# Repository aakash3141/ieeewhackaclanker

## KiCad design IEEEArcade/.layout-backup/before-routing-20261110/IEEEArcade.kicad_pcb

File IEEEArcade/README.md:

# IEEE Arcade

Open **IEEEArcade.kicad_pro** in KiCad. The main schematic, PCB and all five child sheets are required: button_bank_1–4.kicad_sch and scoreboard.kicad_sch. Keep Arcade.kicad_sym, Arcade.pretty, fp-lib-table and sym-lib-table with the project.

## Purchasing and assembly

- [DigiKey cart](Review/DigiKey-cart.html) and [upload CSV](Review/DigiKey-board-cart.csv).
- [Detailed BOM](Review/BOM.html), [part details](Review/DigiKey-board-details.csv), and [optional harness parts](Review/DigiKey-optional-harness.csv).
- [Design review](Review/DESIGN_REVIEW.md), [display wiring](Review/DISPLAY_WIRING.md), and [I/O notes](Review/IO_REVISION.md).
- Project Information retains the original project brief, BOM workbook, manufacturer datasheets, display reference photos and meeting documents.

## PCB status

Read [routing notes](Review/ROUTING.md) and the retained final reports before fabrication. These record the previous checks and unresolved design items; the cleanup did not rerun electrical validation or certify hardware. In particular, the routing notes document a deferred display supply source and existing footprint/parity warnings.

Current artwork: [3D preview](Review/PCB-routed-3D.png), [front copper](Review/PCB-routed-top.svg), [ground plane](Review/PCB-routed-ground.svg).

## Cleanup

On November 13, 2026, historical backups, browser caches, intermediate revision outputs, unused prototype sheets, obsolete scripts, local editor preferences and stale manufacturing outputs were moved to the Windows Recycle Bin. Editable design and library files were verified unchanged, and all six active schematic sheets remain available. Parent-repository Git history was retained. Generate fresh Gerbers/drill files from the current PCB before ordering boards.

The BOM generator and its helper, netlist and mating-part inputs remain in Review so the purchasing artifacts can be regenerated. Historical baseline-dependent audit/placement generators were removed together with their backups.

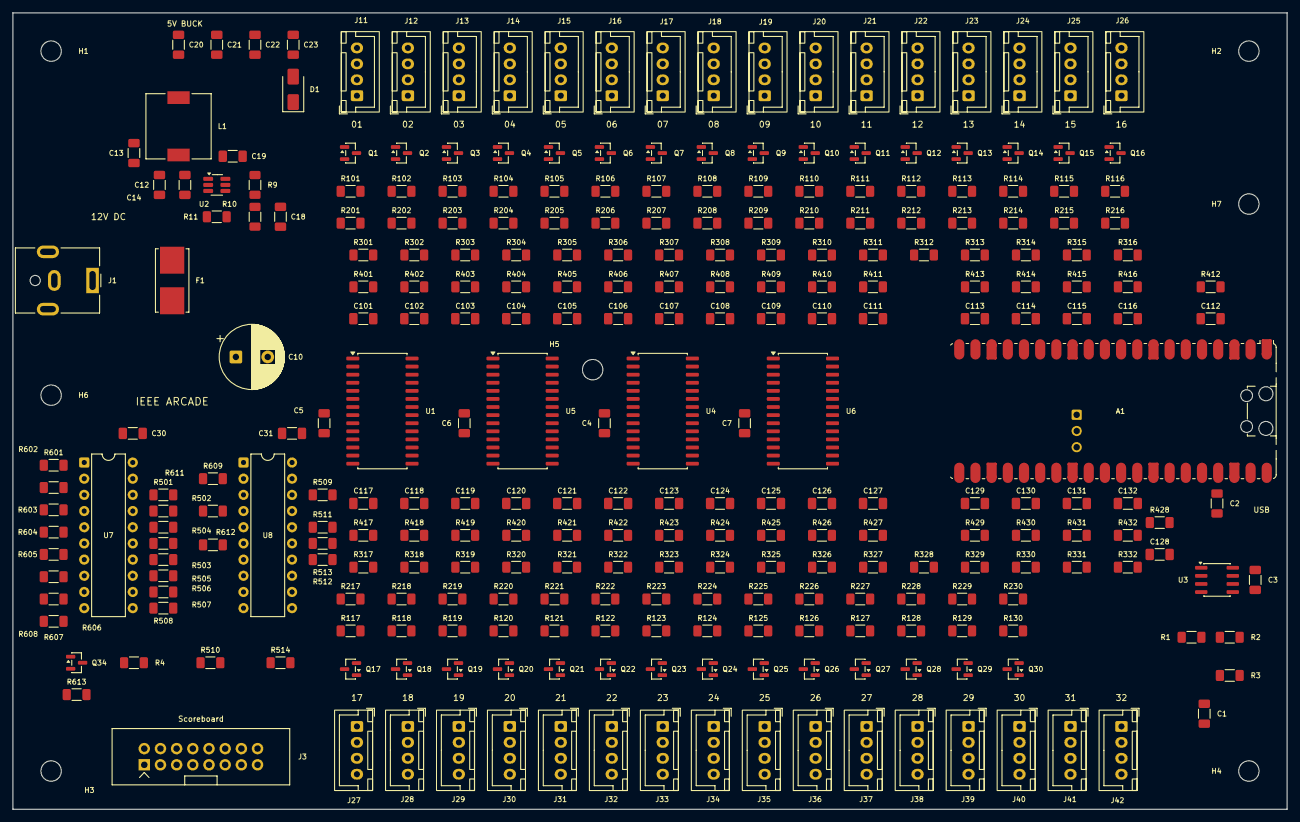
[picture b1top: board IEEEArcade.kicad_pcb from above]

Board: 4 copper layers, 200.0 x 125.0 mm, 292 parts (0 on the bottom side), 206 nets, no tracks yet.

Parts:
A1: Pico 2 W / SC1633; RaspberryPi_Pico_W_SMD_HandSolder
C1, C12, C13, C20, C21, C22, C23: 10u; C_1206_3216Metric_Pad1.33x1.80mm_HandSolder
C2, C3, C4, C5, C6, C7, C14, C19, C30, C31: 100n; C_1206_3216Metric_Pad1.33x1.80mm_HandSolder
C10: 470u; CP_Radial_D10.0mm_P5.00mm
C18: 75p; C_1206_3216Metric_Pad1.33x1.80mm_HandSolder
C101, C102, C103, C104, C105, C106, C107, C108, C109, C110, C111, C112, C113, C114, C115, C116, C117, C118, C119, C120, C121, C122, C123, C124, C125, C126, C127, C128, C129, C130, C131, C132: 10n / 50V; C_1206_3216Metric_Pad1.33x1.80mm_HandSolder
D1: SS14 / VSYS OR-ing; D_SMA
F1: 5A/25VDC fast; Fuseholder_Littelfuse_Nano2_154x
H1, H2, H3, H4, H5, H6, H7: M3 / 3.2mm NPTH; MountingHole_3.2mm_M3
J1: 12VDC; BarrelJack_CUI_PJ-063AH_Horizontal
J3: HUB75 / ABC / pin12 GND; IDC_3M_N2516_2x08
J11, J12, J13, J14, J15, J16, J17, J18, J19, J20, J21, J22, J23, J24, J25, J26, J27, J28, J29, J30, J31, J32, J33, J34, J35, J36, J37, J38, J39, J40: JST XH 4-pin; JST_XH_B4B-XH-A_1x04_P2.50mm_Vertical
J41, J42: MENU input only; JST_XH_B4B-XH-A_1x04_P2.50mm_Vertical
L1: 15uH; L_Wurth_7447714150
Q1, Q2, Q3, Q4, Q5, Q6, Q7, Q8, Q9, Q10, Q11, Q12, Q13, Q14, Q15, Q16, Q17, Q18, Q19, Q20, Q21, Q22, Q23, Q24, Q25, Q26, Q27, Q28, Q29, Q30, Q34: AO3400A; SOT-23
R1, R2, R301, R302, R303, R304, R305, R306, R307, R308, R309, R310, R311, R312, R313, R314, R315, R316, R317, R318, R319, R320, R321, R322, R323, R324, R325, R326, R327, R328, R329, R330, R331, R332: 4.7k; R_1206_3216Metric_Pad1.30x1.75mm_HandSolder
R3, R4, R510, R514: 10k; R_1206_3216Metric_Pad1.30x1.75mm_HandSolder
R9: 511k; R_1206_3216Metric_Pad1.30x1.75mm_HandSolder
R10, R201, R202, R203, R204, R205, R206, R207, R208, R209, R210, R211, R212, R213, R214, R215, R216, R217, R218, R219, R220, R221, R222, R223, R224, R225, R226, R227, R228, R229, R230, R601, R602, R603, R604, R605, R606, R607, R608, R609, R611, R612, R613: 100k; R_1206_3216Metric_Pad1.30x1.75mm_HandSolder
R11: 13.7k; R_1206_3216Metric_Pad1.30x1.75mm_HandSolder
R101, R102, R103, R104, R105, R106, R107, R108, R109, R110, R111, R112, R113, R114, R115, R116, R117, R118, R119, R120, R121, R122, R123, R124, R125, R126, R127, R128, R129, R130, R401, R402, R403, R404, R405, R406, R407, R408, R409, R410, R411, R412, R413, R414, R415, R416, R417, R418, R419, R420, R421, R422, R423, R424, R425, R426, R427, R428, R429, R430, R431, R432: 1k; R_1206_3216Metric_Pad1.30x1.75mm_HandSolder
R501, R502, R503, R504, R505, R506, R507, R508, R509, R511, R512, R513: 33; R_1206_3216Metric_Pad1.30x1.75mm_HandSolder
U1, U4, U5, U6: MCP23017T-E/SO; SOIC-28W_7.5x17.9mm_P1.27mm
U2: TPS54202HDDCR; SOT-23-6_Handsoldering
U3: 24LC256-I/SN; SOIC-8_3.9x4.9mm_P1.27mm
U7, U8: SN74AHCT245N; DIP-20_W7.62mm

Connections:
+3V3: A1.36 (3V3), C1.1, C2.1, C3.1, C4.1, C5.1, C6.1, C7.1, R1.1, R2.1, R3.1, R4.2, R301.1, R302.1, R303.1, R304.1, R305.1, R306.1, R307.1, R308.1, R309.1, R310.1, R311.1, R312.1, R313.1, R314.1, R315.1, R316.1, R317.1, R318.1, R319.1, R320.1, R321.1, R322.1, R323.1, R324.1, R325.1, R326.1, R327.1, R328.1, R329.1, R330.1, R331.1, R332.1, U1.9 (V_{DD}), U1.15 (A0), U3.8 (VCC), U4.9 (V_{DD}), U4.15 (A0), U4.16 (A1), U5.9 (V_{DD}), U5.16 (A1), U6.9 (V_{DD}), U6.17 (A2)
+5V: C18.1, C20.1, C21.1, C22.1, C23.1, D1.2 (A), L1.2, R10.1
+5V_DISPLAY: C30.1, C31.1, R510.1, R514.1, U7.1 (A->B), U7.20 (VCC), U8.1 (A->B), U8.20 (VCC)
+12V: C10.1, C12.1, C13.1, C14.1, F1.2, J11.1, J12.1, J13.1, J14.1, J15.1, J16.1, J17.1, J18.1, J19.1, J20.1, J21.1, J22.1, J23.1, J24.1, J25.1, J26.1, J27.1, J28.1, J29.1, J30.1, J31.1, J32.1, J33.1, J34.1, J35.1, J36.1, J37.1, J38.1, J39.1, J40.1, R9.1, U2.3 (VIN)
/I2C_SCL: A1.20 (GPIO15), R2.2, U1.12 (SCK), U3.6 (SCL), U4.12 (SCK), U5.12 (SCK), U6.12 (SCK)
/I2C_SDA: A1.19 (GPIO14), R1.2, U1.13 (SDA), U3.5 (SDA), U4.13 (SDA), U5.13 (SDA), U6.13 (SDA)
/IO_RESET_N: A1.17 (GPIO13), R3.2, U1.18 (~RESET), U4.18 (~RESET), U5.18 (~RESET), U6.18 (~RESET)
DISP_A: A1.9 (GPIO6), R607.1, U7.8 (A6)
DISP_A_5V: J3.9, R507.2
DISP_B: A1.10 (GPIO7), R608.1, U7.9 (A7)
DISP_B1: A1.4 (GPIO2), R603.1, U7.4 (A2)
DISP_B1_5V: J3.3, R503.2
DISP_B2: A1.7 (GPIO5), R606.1, U7.7 (A5)
DISP_B2_5V: J3.7, R506.2
DISP_BUF_OE_N: Q34.3 (D), R510.2, U7.19 (CE), U8.19 (CE)
DISP_B_5V: J3.10, R508.2
DISP_C: A1.11 (GPIO8), R609.1, U8.2 (A0)
DISP_CLK: A1.14 (GPIO10), R611.1, U8.4 (A2)
DISP_CLK_5V: J3.13, R511.2
DISP_C_5V: J3.11, R509.2
DISP_ENABLE: A1.12 (GPIO9), Q34.1 (G), R613.1
DISP_G1_5V: J3.2, R502.2
DISP_G2: A1.6 (GPIO4), R605.1, U7.6 (A4)
DISP_G2_5V: J3.6, R505.2
DISP_LAT: A1.15 (GPIO11), R612.1, U8.5 (A3)
DISP_LAT_5V: J3.14, R512.2
DISP_OE_N: A1.16 (GPIO12), R4.1, U8.6 (A4)
DISP_OE_N_5V: J3.15, R513.2, R514.2
DISP_R1: A1.1 (GPIO0), R601.1, U7.2 (A0)
DISP_R1_5V: J3.1, R501.2
DISP_R2: A1.5 (GPIO3), R604.1, U7.5 (A3)
DISP_R2_5V: J3.5, R504.2
GND: A1.3 (GND), A1.8 (GND), A1.13 (GND), A1.18 (GND), A1.23 (GND), A1.28 (GND), A1.38 (GND), C1.2, C2.2, C3.2, C4.2, C5.2, C6.2, C7.2, C10.2, C12.2, C13.2, C14.2, C20.2, C21.2, C22.2, C23.2, C30.2, C31.2, C101.2, C102.2, C103.2, C104.2, C105.2, C106.2, C107.2, C108.2, C109.2, C110.2, C111.2, C112.2, C113.2, C114.2, C115.2, C116.2, C117.2, C118.2, C119.2, C120.2, C121.2, C122.2, C123.2, C124.2, C125.2, C126.2, C127.2, C128.2, C129.2, C130.2, C131.2, C132.2, J1.2, J3.4, J3.8, J3.12, J3.16, J11.4, J12.4, J13.4, J14.4, J15.4, J16.4, J17.4, J18.4, J19.4, J20.4, J21.4, J22.4, J23.4, J24.4, J25.4, J26.4, J27.4, J28.4, J29.4, J30.4, J31.4, J32.4, J33.4, J34.4, J35.4, J36.4, J37.4, J38.4, J39.4, J40.4, J41.4, J42.4, Q1.2 (S), Q2.2 (S), Q3.2 (S), Q4.2 (S), Q5.2 (S), Q6.2 (S), Q7.2 (S), Q8.2 (S), Q9.2 (S), Q10.2 (S), Q11.2 (S), Q12.2 (S), Q13.2 (S), Q14.2 (S), Q15.2 (S), Q16.2 (S), Q17.2 (S), Q18.2 (S), Q19.2 (S), Q20.2 (S), Q21.2 (S), Q22.2 (S), Q23.2 (S), Q24.2 (S), Q25.2 (S), Q26.2 (S), Q27.2 (S), Q28.2 (S), Q29.2 (S), Q30.2 (S), Q34.2 (S), R11.2, R201.2, R202.2, R203.2, R204.2, R205.2, R206.2, R207.2, R208.2, R209.2, R210.2, R211.2, R212.2, R213.2, R214.2, R215.2, R216.2, R217.2, R218.2, R219.2, R220.2, R221.2, R222.2, R223.2, R224.2, R225.2, R226.2, R227.2, R228.2, R229.2, R230.2, R601.2, R602.2, R603.2, R604.2, R605.2, R606.2, R607.2, R608.2, R609.2, R611.2, R612.2, R613.2, U1.10 (V_{SS}), U1.16 (A1), U1.17 (A2), U2.1 (GND), U3.1 (A0), U3.2 (A1), U3.3 (A2), U3.4 (GND), U3.7 (WP), U4.10 (V_{SS}), U4.17 (A2), U5.10 (V_{SS}), U5.15 (A0), U5.17 (A2), U6.10 (V_{SS}), U6.15 (A0), U6.16 (A1), U7.10 (GND), U8.3 (A1), U8.7 (A5), U8.8 (A6), U8.9 (A7), U8.10 (GND)
LAMP_01: R101.2, U1.28 (GPA7)
LAMP_02: R102.2, U1.8 (GPB7)
LAMP_03: R103.2, U5.23 (GPA2)
LAMP_04: R104.2, U5.24 (GPA3)
LAMP_05: R105.2, U5.25 (GPA4)
LAMP_06: R106.2, U5.26 (GPA5)
LAMP_07: R107.2, U5.27 (GPA6)
LAMP_08: R108.2, U5.28 (GPA7)
LAMP_09: R109.1, U5.1 (GPB0)
LAMP_10: R110.1, U5.2 (GPB1)
LAMP_11: R111.1, U5.3 (GPB2)
LAMP_12: R112.1, U5.4 (GPB3)
LAMP_13: R113.1, U5.5 (GPB4)
LAMP_14: R114.1, U5.6 (GPB5)
LAMP_15: R115.1, U5.7 (GPB6)
LAMP_16: R116.1, U5.8 (GPB7)
LAMP_17: R117.1, U4.28 (GPA7)
LAMP_18: R118.1, U4.8 (GPB7)
LAMP_19: R119.1, U6.23 (GPA2)
LAMP_20: R120.1, U6.24 (GPA3)
LAMP_21: R121.1, U6.25 (GPA4)
LAMP_22: R122.1, U6.26 (GPA5)
LAMP_23: R123.1, U6.27 (GPA6)
LAMP_24: R124.1, U6.28 (GPA7)
LAMP_25: R125.1, U6.1 (GPB0)
LAMP_26: R126.1, U6.2 (GPB1)
LAMP_27: R127.1, U6.3 (GPB2)
LAMP_28: R128.1, U6.4 (GPB3)
LAMP_29: R129.1, U6.5 (GPB4)
LAMP_30: R130.1, U6.6 (GPB5)
unnamed: A1.39 (VSYS), D1.1 (K)
unnamed: F1.1, J1.1
unnamed: J11.2, Q1.3 (D)
unnamed: J11.3, R301.2, R401.2
unnamed: J12.2, Q2.3 (D)
unnamed: J12.3, R302.2, R402.2
unnamed: J13.2, Q3.3 (D)
unnamed: J13.3, R303.2, R403.2
unnamed: J14.2, Q4.3 (D)
unnamed: J14.3, R304.2, R404.2
unnamed: J15.2, Q5.3 (D)
unnamed: J15.3, R305.2, R405.2
unnamed: J16.2, Q6.3 (D)
unnamed: J16.3, R306.2, R406.2
unnamed: J17.2, Q7.3 (D)
unnamed: J17.3, R307.2, R407.2
unnamed: J18.2, Q8.3 (D)
unnamed: J18.3, R308.2, R408.2
unnamed: J19.2, Q9.3 (D)
unnamed: J19.3, R309.2, R409.1
unnamed: J20.2, Q10.3 (D)
unnamed: J20.3, R310.2, R410.1
unnamed: J21.2, Q11.3 (D)
unnamed: J21.3, R311.2, R411.1
unnamed: J22.2, Q12.3 (D)
unnamed: J22.3, R312.2, R412.1
unnamed: J23.2, Q13.3 (D)
unnamed: J23.3, R313.2, R413.1
unnamed: J24.2, Q14.3 (D)
unnamed: J24.3, R314.2, R414.1
unnamed: J25.2, Q15.3 (D)
unnamed: J25.3, R315.2, R415.1
unnamed: J26.2, Q16.3 (D)
unnamed: J26.3, R316.2, R416.1
unnamed: J27.2, Q17.3 (D)
unnamed: J27.3, R317.2, R417.1
unnamed: J28.2, Q18.3 (D)
unnamed: J28.3, R318.2, R418.1
unnamed: J29.2, Q19.3 (D)
unnamed: J29.3, R319.2, R419.1
unnamed: J30.2, Q20.3 (D)
unnamed: J30.3, R320.2, R420.1
unnamed: J31.2, Q21.3 (D)
unnamed: J31.3, R321.2, R421.1
unnamed: J32.2, Q22.3 (D)
unnamed: J32.3, R322.2, R422.1
unnamed: J33.2, Q23.3 (D)
unnamed: J33.3, R323.2, R423.1
unnamed: J34.2, Q24.3 (D)
unnamed: J34.3, R324.2, R424.1
unnamed: J35.2, Q25.3 (D)
unnamed: J35.3, R325.2, R425.1
unnamed: J36.2, Q26.3 (D)
unnamed: J36.3, R326.2, R426.1
unnamed: J37.2, Q27.3 (D)
unnamed: J37.3, R327.2, R427.1
unnamed: J38.2, Q28.3 (D)
unnamed: J38.3, R328.2, R428.1
unnamed: J39.2, Q29.3 (D)
unnamed: J39.3, R329.2, R429.1
unnamed: J40.2, Q30.3 (D)
unnamed: J40.3, R330.2, R430.1
unnamed: J41.3, R331.2, R431.1
unnamed: J42.3, R332.2, R432.1
unnamed: Q1.1 (G), R101.1, R201.1
unnamed: Q2.1 (G), R102.1, R202.1
unnamed: Q3.1 (G), R103.1, R203.1
unnamed: Q4.1 (G), R104.1, R204.1
unnamed: Q5.1 (G), R105.1, R205.1
unnamed: Q6.1 (G), R106.1, R206.1
unnamed: Q7.1 (G), R107.1, R207.1
unnamed: Q8.1 (G), R108.1, R208.1
unnamed: Q9.1 (G), R109.2, R209.1
unnamed: Q10.1 (G), R110.2, R210.1
unnamed: Q11.1 (G), R111.2, R211.1
unnamed: Q12.1 (G), R112.2, R212.1
unnamed: Q13.1 (G), R113.2, R213.1
unnamed: Q14.1 (G), R114.2, R214.1
unnamed: Q15.1 (G), R115.2, R215.1
unnamed: Q16.1 (G), R116.2, R216.1
unnamed: Q17.1 (G), R117.2, R217.1
unnamed: Q18.1 (G), R118.2, R218.1
unnamed: Q19.1 (G), R119.2, R219.1
unnamed: Q20.1 (G), R120.2, R220.1
unnamed: Q21.1 (G), R121.2, R221.1
unnamed: Q22.1 (G), R122.2, R222.1
unnamed: Q23.1 (G), R123.2, R223.1
unnamed: Q24.1 (G), R124.2, R224.1
unnamed: Q25.1 (G), R125.2, R225.1
unnamed: Q26.1 (G), R126.2, R226.1
unnamed: Q27.1 (G), R127.2, R227.1
unnamed: Q28.1 (G), R128.2, R228.1
unnamed: Q29.1 (G), R129.2, R229.1
unnamed: Q30.1 (G), R130.2, R230.1
unnamed: C19.1, U2.6 (BOOT)
unnamed: R9.2, U2.5 (EN)
unnamed: C18.2, R10.2, R11.1, U2.4 (FB)
unnamed: C19.2, L1.1, U2.2 (SW)
unnamed: R602.1, U7.3 (A1)
unnamed: R501.1, U7.18 (B0)
unnamed: R502.1, U7.17 (B1)
unnamed: R503.1, U7.16 (B2)
unnamed: R504.1, U7.15 (B3)
unnamed: R505.1, U7.14 (B4)
unnamed: R506.1, U7.13 (B5)
unnamed: R507.1, U7.12 (B6)
unnamed: R508.1, U7.11 (B7)
unnamed: R509.1, U8.18 (B0)
unnamed: R511.1, U8.16 (B2)
unnamed: R512.1, U8.15 (B3)
unnamed: R513.1, U8.14 (B4)
SW_01: C101.1, R401.1, U1.21 (GPA0)
SW_02: C102.1, R402.1, U1.22 (GPA1)
SW_03: C103.1, R403.1, U1.23 (GPA2)
SW_04: C104.1, R404.1, U1.24 (GPA3)
SW_05: C105.1, R405.1, U1.25 (GPA4)
SW_06: C106.1, R406.1, U1.26 (GPA5)
SW_07: C107.1, R407.1, U1.27 (GPA6)
SW_08: C108.1, R408.1, U1.1 (GPB0)
SW_09: C109.1, R409.2, U1.2 (GPB1)
SW_10: C110.1, R410.2, U1.3 (GPB2)
SW_11: C111.1, R411.2, U1.4 (GPB3)
SW_12: C112.1, R412.2, U1.5 (GPB4)
SW_13: C113.1, R413.2, U1.6 (GPB5)
SW_14: C114.1, R414.2, U1.7 (GPB6)
SW_15: C115.1, R415.2, U4.21 (GPA0)
SW_16: C116.1, R416.2, U4.22 (GPA1)
SW_17: C117.1, R417.2, U4.23 (GPA2)
SW_18: C118.1, R418.2, U4.24 (GPA3)
SW_19: C119.1, R419.2, U4.25 (GPA4)
SW_20: C120.1, R420.2, U4.26 (GPA5)
SW_21: C121.1, R421.2, U4.27 (GPA6)
SW_22: C122.1, R422.2, U4.1 (GPB0)
SW_23: C123.1, R423.2, U4.2 (GPB1)
SW_24: C124.1, R424.2, U4.3 (GPB2)
SW_25: C125.1, R425.2, U4.4 (GPB3)
SW_26: C126.1, R426.2, U4.5 (GPB4)
SW_27: C127.1, R427.2, U4.6 (GPB5)
SW_28: C128.1, R428.2, U4.7 (GPB6)
SW_29: C129.1, R429.2, U5.21 (GPA0)
SW_30: C130.1, R430.2, U5.22 (GPA1)
SW_31: C131.1, R431.2, U6.21 (GPA0)
SW_32: C132.1, R432.2, U6.22 (GPA1)

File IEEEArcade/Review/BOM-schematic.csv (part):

"Reference","Value","Quantity","Manufacturer","MPN","DigiKey","DigiKey URL","Datasheet","Footprint","Assembly","Verification"
"A1","Pico 2 W / SC1633","1","Raspberry Pi","SC1633","2648-SC1633CT-ND","https://www.digikey.com/en/products/detail/raspberry-pi/SC16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","https://datasheets.raspberrypi.com/picow/pico-2-w-datasheet.pdf","Module:RaspberryPi_Pico_W_SMD_HandSolder","On PCB","Pico 2 W datasheet pinout/package checked; KiCad W footprint explicitly supports Pico 2 W; DigiKey in stock 2026-11-05"
"C1,C12,C13,C20-C23","10u","7","KEMET","C1206C106K3RACTU","399-C1206C106K3RACTUCT-ND","https://www.digikey.com/en/products/detail/kemet/C1206C106K3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","https://search.kemet.com/component-documentation/download/sp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","Capacitor_SMD:C_1206_3216Metric_Pad1.33x1.80mm_HandSolder","On PCB","Datasheet pinout/package checked; DigiKey stock seen 2026-11-04"
"C2-C7,C14,C19,C30,C31","100n","10","KEMET","C1206C104K5RACTU","399-C1206C104K5RACTUCT-ND","https://www.digikey.com/en/products/detail/kemet/C1206C104K5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","https://search.kemet.com/component-documentation/download/sp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","Capacitor_SMD:C_1206_3216Metric_Pad1.33x1.80mm_HandSolder","On PCB","Datasheet pinout/package checked; DigiKey stock seen 2026-11-04"
"C10","470u","1","Panasonic Industry","EEU-FR1E471","P14419-ND","https://www.digikey.com/en/products/detail/panasonic-industr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","https://industrial.panasonic.com/cdbs/www-data/pdf/RDF0000/A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","Capacitor_THT:CP_Radial_D10.0mm_P5.00mm","On PCB","Datasheet pinout/package checked; DigiKey stock seen 2026-11-04"
"C18","75p","1","KEMET","C1206C750J5GACTU","399-14710-1-ND","https://www.digikey.com/en/products/detail/kemet/C1206C750J5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","https://search.kemet.com/component-documentation/download/sp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","Capacitor_SMD:C_1206_3216Metric_Pad1.33x1.80mm_HandSolder","On PCB","Datasheet pinout/package checked; DigiKey stock seen 2026-11-04"
"C101-C132","10n / 50V","32","KEMET","C1206C103K5RACTU","399-C1206C103K5RACTUCT-ND","https://www.digikey.com/en/products/detail/kemet/C1206C103K5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","https://search.kemet.com/component-documentation/download/sp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","Capacitor_SMD:C_1206_3216Metric_Pad1.33x1.80mm_HandSolder","On PCB","Datasheet pinout/package checked; DigiKey stock seen 2026-11-04"
"D1","SS14 / VSYS OR-ing","1","Vishay General Semiconductor","SS14-E3/61T","SS14-E3/61TGICT-ND","https://www.digikey.com/en/products/detail/vishay-general-se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","https://www.vishay.com/docs/88746/ss12.pdf","Diode_SMD:D_SMA","On PCB","Datasheet pinout/package checked; DigiKey stock seen 2026-11-04"
"F1","5A/25VDC fast","1","Littelfuse","0154005.DR","F1228CT-ND","https://www.digikey.com/en/products/detail/littelfuse-inc/01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","https://www.littelfuse.com/assetdocs/littelfuse-fuse-154-ser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","Fuse:Fuseholder_Littelfuse_Nano2_154x","Holder supplied preloaded with 5 A fuse","Datasheet pinout/package checked; DigiKey stock seen 2026-11-04"
"J1","12VDC","1","Same Sky","PJ-063AH","CP-063AH-ND","https://www.digikey.com/en/products/detail/same-sky-formerly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","https://www.sameskydevices.com/product/resource/pj-063ah.pdf","Connector_BarrelJack:BarrelJack_CUI_PJ-063AH_Horizontal","On PCB","Exact-MPN KiCad footprint, 2 contacts / 8A / 24V confirmed; manufacturer mechanical PDF retrieval blocked, dimensional cross-check remains open. Actual adapter plug/polarity unverified."
"J3","HUB75 / ABC / pin12 GND","1","3M","N2516-6002-RB","MHC16K-ND","https://www.digikey.com/en/products/detail/3m/N2516-6002-RB/755178","https://multimedia.3m.com/mws/media/330367O/3m-four-wall-hea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","Arcade:IDC_3M_N2516_2x08","16-way straight-through IDC to panel INPUT; OUTPUT header unused for one panel","Signal assignment read from DisplayConnections1.png: pin12 GND, not D; check mating-view pin1 on actual input header"
"J4","EXT 5V INPUT / BUFFERS ONLY","1","JST Sales America","B2B-XH-A","455-B2B-XH-A-ND","https://www.digikey.com/en/products/detail/jst-sales-america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","https://www.jst-mfg.com/product/pdf/eng/eXH.pdf","Connector_JST:JST_XH_B2B-XH-A_1x02_P2.50mm_Vertical","Input from external regulated 5V display supply; panel fed directly by separate high-current harness","Board-side XH mate verified; J4 is NOT the photographed 4-contact panel power connector"
"J11-J40","JST XH 4-pin","30","JST Sales America","B4B-XH-A","455-B4B-XH-A-ND","https://www.digikey.com/en/products/detail/jst-sales-america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","https://www.jst-mfg.com/product/pdf/eng/eXH.pdf","Connector_JST:JST_XH_B4B-XH-A_1x04_P2.50mm_Vertical","PCB header; mating XHP-4 + 4 SXH-001T-P0.6","Datasheet pinout/package checked; DigiKey stock seen 2026-11-04"
"J41,J42","MENU input only","2","JST Sales America","B4B-XH-A","455-B4B-XH-A-ND","https://www.digikey.com/en/products/detail/jst-sales-america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","https://www.jst-mfg.com/product/pdf/eng/eXH.pdf","Connector_JST:JST_XH_B4B-XH-A_1x04_P2.50mm_Vertical","PCB header; mating XHP-4 + 4 SXH-001T-P0.6","Input-only menu button. Pins 1/2 unused; no lamp supply or driver. Pin3 NO, pin4 COM/GND."
"L1","15uH","1","Wurth Elektronik","7447714150","732-2990-1-ND","https://www.digikey.com/en/products/detail/w%C3%BCrth-elektr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","https://www.we-online.com/components/products/datasheet/7447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","Arcade:L_Wurth_7447714150","On PCB","Datasheet pinout/package checked; DigiKey stock seen 2026-11-04"
"Q1-Q30,Q34","AO3400A","31","Alpha & Omega Semiconductor","AO3400A","785-1000-1-ND","https://www.digikey.com/en/products/detail/alpha-omega-semic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","https://www.aosmd.com/res/data_sheets/AO3400A.pdf","Package_TO_SOT_SMD:SOT-23","On PCB,On PCB; display buffer enable, GPIO9 HIGH enables","Datasheet pinout/package checked; DigiKey stock seen 2026-11-04"
"R1,R2,R301-R332","4.7k","34","YAGEO","RC1206FR-074K7L","311-4.70KFRCT-ND","https://www.digikey.com/en/products/detail/yageo/RC1206FR-07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","https://yageogroup.com/content/datasheet/asset/file/PYU-RC_G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","Resistor_SMD:R_1206_3216Metric_Pad1.30x1.75mm_HandSolder","On PCB","Datasheet pinout/package checked; DigiKey stock seen 2026-11-04"
"R3,R4,R510,R514","10k","4","YAGEO","RC1206FR-0710KL","311-10.0KFRCT-ND","https://www.digikey.com/en/products/detail/yageo/RC1206FR-07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","https://yageogroup.com/content/datasheet/asset/file/PYU-RC_G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","Resistor_SMD:R_1206_3216Metric_Pad1.30x1.75mm_HandSolder","On PCB,On PCB; keeps panel OE inactive when buffers disabled","Datasheet pinout/package checked; DigiKey stock seen 2026-11-04"
"R9","511k","1","YAGEO","RC1206FR-07511KL","311-511KFRCT-ND","https://www.digikey.com/en/products/detail/yageo/RC1206FR-07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","https://yageogroup.com/content/datasheet/asset/file/PYU-RC_G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","Resistor_SMD:R_1206_3216Metric_Pad1.30x1.75mm_HandSolder","On PCB","Datasheet pinout/package checked; DigiKey stock seen 2026-11-04"
"R10,R201-R230,R601-R612","100k","43","YAGEO","RC1206FR-07100KL","311-100KFRCT-ND","https://www.digikey.com/en/products/detail/yageo/RC1206FR-07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","https://yageogroup.com/content/datasheet/asset/file/PYU-RC_G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","Resistor_SMD:R_1206_3216Metric_Pad1.30x1.75mm_HandSolder","On PCB","Datasheet pinout/package checked; DigiKey stock seen 2026-11-04"
"R11","13.7k","1","YAGEO","RC1206FR-0713K7L","311-13.7KFRCT-ND","https://www.digikey.com/en/products/detail/yageo/RC1206FR-07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","https://yageogroup.com/content/datasheet/asset/file/PYU-RC_G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","Resistor_SMD:R_1206_3216Metric_Pad1.30x1.75mm_HandSolder","On PCB","Datasheet pinout/package checked; DigiKey stock seen 2026-11-04"
"R101-R130,R401-R432","1k","62","YAGEO","RC1206FR-071KL","311-1.00KFRCT-ND","https://www.digikey.com/en/products/detail/yageo/RC1206FR-07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","https://yageogroup.com/content/datasheet/asset/file/PYU-RC_G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","Resistor_SMD:R_1206_3216Metric_Pad1.30x1.75mm_HandSolder","On PCB","Datasheet pinout/package checked; DigiKey stock seen 2026-11-04"
"R501-R509,R511-R513","33","12","YAGEO","RC1206FR-0733RL","311-33.0FRCT-ND","https://www.digikey.com/en/products/detail/yageo/RC1206FR-07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","https://yageogroup.com/content/datasheet/asset/file/PYU-RC_G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","Resistor_SMD:R_1206_3216Metric_Pad1.30x1.75mm_HandSolder","On PCB","Datasheet pinout/package checked; DigiKey stock seen 2026-11-04"
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
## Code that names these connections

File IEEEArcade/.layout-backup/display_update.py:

from pathlib import Path
import re,uuid
exec(Path('display_inspect.py').read_text().split('for file in')[0])
def uid():return str(uuid.uuid4())
def fmt(v):return f'{v:.5f}'.rstrip('0').rstrip('.')
def at(b):return tuple(map(float,re.search(r'\(at ([^ ]+) ([^ ]+) ([^)]+)\)',b).groups()))
def move(b,x,y,angle=None):
 ox,oy,oa=at(b); dx=x-ox;dy=y-oy
 b=re.sub(r'\(at ([^ ]+) ([^ ]+) ([^)]+)\)',lambda m:f'(at {fmt(float(m[1])+dx)} {fmt(float(m[2])+dy)} {m[3]})',b)
 if angle is not None:b=re.sub(r'\(at [^ ]+ [^ ]+ [^)]+\)',f'(at {fmt(x)} {fmt(y)} {angle})',b,count=1)
 return b

def prop(b,k,v):
 return re.sub(r'(\(property "'+re.escape(k)+r'" )"(?:\\.|[^"\\])*"',lambda m:m[1]+'"'+v.replace('\\','\\\\').replace('"','\\"').replace('\n','\\n')+'"',b,count=1)
def fresh(b):return re.sub(r'\(uuid "[^"]+"\)',lambda m:f'(uuid "{uid()}")',b)
def label(name,x,y,angle=0):
 return f'(global_label "{name}" (shape bidirectional) (at {fmt(x)} {fmt(y)} {angle}) (effects (font (size 1.05 1.05)) (justify {"left" if angle==0 else "right"})) (uuid "{uid()}"))'
def wire(x1,y1,x2,y2):return f'(wire (pts (xy {fmt(x1)} {fmt(y1)}) (xy {fmt(x2)} {fmt(y2)})) (stroke (width 0) (type default)) (uuid "{uid()}"))'
def nc(x,y):return f'(no_connect (at {fmt(x)} {fmt(y)}) (uuid "{uid()}"))'
def text(t,x,y,size=1.05):
 t=t.replace('\\','\\\\').replace('"','\\"').replace('\n','\\n')
 return f'(text "{t}" (exclude_from_sim no) (at {fmt(x)} {fmt(y)} 0) (effects (font (size {size} {size})) (justify left)) (uuid "{uid()}"))'
root=Path('IEEEArcade.kicad_sch').read_text();s=Path('scoreboard.kicad_sch').read_text();bs=list(blocks(s));rb=list(blocks(root));bank=list(blocks(Path('button_bank_1.kicad_sch').read_text()))
syms={ref(b):b for b in bs if b.startswith('(symbol')}
path=re.search(r'\(path "([^"]+)"',syms['R4'])[1]
def clone(b,nr,x,y):
 oldref=ref(b);b=fresh(move(b,x,y));b=prop(b,'Reference',nr)
 b=b.replace(f'(reference "{oldref}")',f'(reference "{nr}")')
 b=re.sub(r'\(path "[^"]+"',f'(path "{path}"',b)
 return b
# Use existing verified 10k and 100k parts; no new resistor SKU.
r10=syms['R4'];q=next(b for b in bank if ref(b)=='Q1' and b.startswith('(symbol'))
q33=clone(q,'Q33',292.1,248.92)
q33=prop(q33,'Assembly','On PCB; display buffer enable, GPIO9 HIGH enables')
# Existing R510 is repurposed as 10k buffer-disable pull-up.
r510=clone(r10,'R510',294.64,232.41)
# Keep R510's symbol/pin identities for board association.
uold=re.findall(r'\(uuid "([^"]+)"\)',syms['R510']);unew=re.findall(r'\(uuid "([^"]+)"\)',r510)
for a,b in zip(unew,uold):r510=r510.replace(a,b)
r514=clone(r10,'R514',248.92,240.03)
r514=prop(r514,'Assembly','On PCB; keeps panel OE inactive when buffers disabled')
new=[]
for b in bs:
 if b.startswith('(lib_symbols'):
  # Add the existing MOSFET definition and PWR_FLAG for external supply.
  blib=next(x for x in bank if x.startswith('(lib_symbols'));rlib=next(x for x in rb if x.startswith('(lib_symbols'))
  extra=[next(x for x in blocks(blib) if x.startswith('(symbol "Transistor_FET:AO3400A"')),next(x for x in blocks(rlib) if x.startswith('(symbol "power:PWR_FLAG"'))]
  b=b[:-1]+'\n\t\t'+'\n\t\t'.join(extra)+'\n\t)'
 elif b.startswith('(title_block'): b=b.replace('Provisional 16-pin external scoreboard','Photo-matched HUB75 scoreboard / A-B-C scan')
 elif b.startswith('(symbol'):
  r=ref(b)
  if r=='R510':b=r510
  elif r in ['#PWR0055','#PWR0069']:b=label('DISP_BUF_OE_N',*at(b)[:2],180)
  elif '"power:+5V"' in b:b=label('+5V_DISPLAY',*at(b)[:2],180)
  elif r=='J3':
   b=prop(b,'Value','HUB75 / ABC / pin12 GND')
   b=prop(b,'Verification','Signal assignment read from DisplayConnections1.png: pin12 GND, not D; check mating-view pin1 on actual input header')
   b=prop(b,'Assembly','16-way straight-through IDC to panel INPUT; OUTPUT header unused for one panel')
  elif r=='J4':
   b=prop(b,'Value','EXT 5V INPUT / BUFFERS ONLY')
   b=prop(b,'Assembly','Input from external regulated 5V display supply; panel fed directly by separate high-current harness')
   b=prop(b,'Verification','Board-side XH mate verified; J4 is NOT the photographed 4-contact panel power connector')
 elif b.startswith('(global_label "DISP_D"'):
  b=label('DISP_ENABLE',48.26,177.8,180)
 elif b.startswith('(global_label "DISP_D_5V"'):
  if at(b)[0]>350:b=label('GND',*at(b)[:2])
  else:continue
 elif b.startswith('(wire'):
  pts=[tuple(map(float,m)) for m in re.findall(r'\(xy ([^ ]+) ([^)]+)\)',b)]
  if pts in [[(193.04,177.8),(283.21,177.8)],[(290.83,177.8),(307.34,177.8)],[(167.64,177.8),(48.26,177.8)]]:continue
 elif b.startswith('(text'):
  if 'A -> B: DIR high' in b:
   b=re.sub(r'\(text "(?:\\.|[^"\\])*"',lambda m:'(text "DIR high: A-to-B. /OE controlled by DISP_BUF_OE_N.\\nUnused inputs grounded; unused outputs left open."',b,count=1)
  elif 'EXTERNAL SCOREBOARD |' in b:
   b=prop(b,'dummy','dummy') # text retains UUID and placement below
   b=re.sub(r'\(text "(?:\\.|[^"\\])*"','(text "RGB SCOREBOARD | PHOTO-MATCHED HUB75 / A-B-C"',b,count=1)
  elif 'User requested an expected connector' in b:
   b=re.sub(r'\(text "(?:\\.|[^"\\])*"',lambda m:'(text "Photo: DR1/DG1/DB1, DR2/DG2/DB2, A/B/C, CLK, STB, OE. Pin12 = GND (NOT D).\\nPico PIO refresh: 6 RGB + 3 address + CLK/LAT/OE; no I2C expander. GP9 enables buffers."',b,count=1)
  elif 'J4: 1=+5 V' in b:
   b=text('J4 INPUT: 1=external +5V, 2=GND.\nPowers AHCT buffers ONLY.\nPanel power: direct external PSU\nto VCC/GND power contacts.\nDo not bridge to board +5V buck.\nConfirm panel voltage/current.\n5V is a design assumption.',337.82,198.12)
  elif 'R501..R513:' in b:
   b=text('R501..R509, R511..R513: 33 ohms. R510: 10k buffer-disable pull-up; R610: 100k GP9 pull-down.\nQ33 enables buffers only when GP9 HIGH; R514 holds panel OE HIGH when buffers are disabled.\nInitialize OE HIGH, CLK/LAT LOW and row/data outputs; then enable GP9. Use PIO/DMA scan refresh.\nExternal regulated display supply: direct power harness to panel, common GND to J4/J3. Voltage/current and scan mapping need confirmation.',20,269.24)
 new.append(b)
new += [nc(193.04,177.8),label('GND',167.64,177.8,180),q33,r514,
 label('+5V_DISPLAY',294.64,226.06,180),wire(294.64,226.06,294.64,228.6),
 wire(294.64,236.22,294.64,240.03),wire(294.64,240.03,294.64,243.84),label('DISP_BUF_OE_N',294.64,240.03),
 f'(junction (at 294.64 240.03) (diameter 0) (color 0 0 0 0) (uuid "{uid()}"))',
 wire(287.02,248.92,276.86,248.92),label('DISP_ENABLE',276.86,248.92,180),
 wire(294.64,254,294.64,259.08),label('GND',294.64,259.08),
 label('+5V_DISPLAY',248.92,231.14,180),wire(248.92,231.14,248.92,236.22),
 wire(248.92,243.84,248.92,248.92),label('DISP_OE_N_5V',248.92,248.92),
 text('RESET-SAFE DISPLAY ENABLE\nGP9 LOW / floating: blank\nGP9 HIGH: PIO owns panel',225,216.0),
 text('J3 -> panel INPUT (follow data-flow arrow).\nHeader pin rows, mating orientation checked:\n 1 R1   2 G1     3 B1   4 GND\n 5 R2   6 G2     7 B2   8 GND\n 9 A   10 B     11 C   12 GND\n13 CLK 14 STB   15 OE  16 GND\nSTB = LAT. OE is active LOW.\nPanel OUTPUT: leave open, or cascade.\nPower: all VCC contacts to supply +;\nall GND contacts to supply return.\nPhoto does not establish power pin numbers.',310,118.11,0.95)]
flag=next(b for b in rb if b.startswith('(symbol') and ref(b)=='#FLG01')
new.append(clone(flag,'#FLG03',358.14,152.4))
# Preserve existing sheet formatting, with new blocks appended.
Path('scoreboard.kicad_sch').write_text('(kicad_sch\n\t'+'\n\t'.join(new)+'\n)\n')
root=root.replace('(global_label "DISP_D"','(global_label "DISP_ENABLE"').replace('"Scoreboard (PROVISIONAL)"','"Scoreboard (HUB75 ABC)"')
# Describe freed address-D output repurposing at the Pico label.
Path('IEEEArcade.kicad_sch').write_text(root)
print('Updated scoreboard and root sheet; retained other sheets untouched.')

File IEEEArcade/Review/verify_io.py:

"""Independent checks against the KiCad-exported netlist, datasheet pin maps and installed footprints."""
from pathlib import Path
import xml.etree.ElementTree as ET,json,re,collections,sys
sys.dont_write_bytecode=True
sys.path.insert(0,str(Path(__file__).parent))
from schematic_tools import parse,prop
r=ET.parse('Review/after-io.net').getroot();before=ET.parse('Review/before-io.net').getroot()
components={c.get('ref'):c for c in r.findall('./components/comp')}
nets={n.get('name'):{(x.get('ref'),x.get('pin')) for x in n.findall('node')} for n in r.findall('./nets/net')}
pinnet={p:name for name,nodes in nets.items() for p in nodes}
checks=[]
def check(ok,message):
 assert ok,message
 checks.append('PASS: '+message)
expanders={'U1':0x20,'U4':0x23,'U5':0x21,'U6':0x22}
for ref,addr in expanders.items():
 check(components[ref].findtext('value')=='MCP23017T-E/SO',ref+' is MCP23017T-E/SO')
 for pin,net in {'9':'+3V3','10':'GND','12':'/I2C_SCL','13':'/I2C_SDA','18':'/IO_RESET_N'}.items():check(pinnet[(ref,pin)]==net,f'{ref} pin{pin} = {net}')
 actual=0x20+sum((1<<i) if pinnet[(ref,str(15+i))]=='+3V3' else 0 for i in range(3))
 check(all(pinnet[(ref,str(15+i))] in ['GND','+3V3'] for i in range(3)) and actual==addr,f'{ref} A2:A0 produce unique address {addr:#04x}')
 for pin in ['11','14','19','20']:
  check(pinnet[(ref,pin)].startswith('unconnected-') and len(nets[pinnet[(ref,pin)]])==1,f'{ref} NC/unused interrupt pin{pin} intentionally open')
for i in range(1,33):
 name=f'SW_{i:02}';nodes=nets[name];chip=[(ref,p) for ref,p in nodes if ref in expanders]
 check(len(chip)==1 and chip[0][1] not in ['8','28'],f'{name} has one input-capable MCP23017 pin')
 check(len(nodes)==3 and {ref for ref,p in nodes}=={chip[0][0],f'R{400+i}',f'C{100+i}'},f'{name} connects only expander, 1k series resistor and 10nF filter')
 check(components[f'R{400+i}'].findtext('value')=='1k' and components[f'C{100+i}'].findtext('value').startswith('10n'),f'{name} RC values retained')
 raw=pinnet[(f'J{10+i}','3')];rawnodes=nets[raw]
 check({ref for ref,p in rawnodes}=={f'J{10+i}',f'R{300+i}',f'R{400+i}'},f'{name} connector NO has dedicated pull-up and series filter')
 check(pinnet[(f'J{10+i}','4')]=='GND' and pinnet[(f'R{300+i}','1')]=='+3V3',f'{name} COM grounded, pull-up to 3.3V')
for i in range(1,31):
 name=f'LAMP_{i:02}';nodes=nets[name];chip=[x for x in nodes if x[0] in expanders]
 check(len(nodes)==2 and len(chip)==1 and any(x[0]==f'R{100+i}' for x in nodes),name+' has one expander output and one gate resistor')
 check(pinnet[(f'J{10+i}','1')]=='+12V' and pinnet[(f'J{10+i}','2')]==pinnet[(f'Q{i}','3')],name+' harness has 12V anode / MOSFET drain cathode')
 check(pinnet[(f'Q{i}','2')]=='GND',name+' MOSFET source grounded')
for name,nodes in nets.items():check(not re.search(r'(SW_\d+_FILT|LAMP_\d+_EN|LAMP_3[12](?:$|_))',name),'No obsolete channel label on '+name)
for ref in ['J41','J42']:
 for pin in ['1','2']:check(pinnet[(ref,pin)].startswith('unconnected-') and len(nets[pinnet[(ref,pin)]])==1,ref+' menu lamp pin'+pin+' disconnected')
for ref in ['Q31','Q32','R131','R132','R231','R232']:check(ref not in components,ref+' surplus menu lamp component removed')
for pin in ['7','8']:check(pinnet[('U6',pin)].startswith('unconnected-'),'U6 spare pin'+pin+' intentionally unused')
for pin,name in {'1':'GND','2':'GND','3':'GND','4':'GND','5':'/I2C_SDA','6':'/I2C_SCL','7':'GND','8':'+3V3'}.items():check(pinnet[('U3',pin)]==name,f'24LC256 U3 pin{pin} = {name}')
for ref,pin,net in [('R1','1','+3V3'),('R1','2','/I2C_SDA'),('R2','1','+3V3'),('R2','2','/I2C_SCL'),('R3','1','+3V3'),('R3','2','/IO_RESET_N')]:check(pinnet[(ref,pin)]==net,f'{ref} pin{pin} {net}')
check(components['R1'].findtext('value')==components['R2'].findtext('value')=='4.7k','I2C has one 4.7k pull-up per line')
check(components['R3'].findtext('value')=='10k','Reset has 10k pull-up')
for ref in ['C3','C4','C5','C6','C7']:check(components[ref].findtext('value')=='100n' and pinnet[(ref,'1')]=='+3V3' and pinnet[(ref,'2')]=='GND',ref+' IC bypass 100nF across 3.3V and GND')
# Compare net equivalence classes without net names, excluding deliberately modified devices.
removed={'Q31','Q32','R131','R132','R231','R232'}
def groups(root):
 result=set()
 for n in root.findall('./nets/net'):
  pts=frozenset((x.get('ref'),x.get('pin')) for x in n.findall('node') if x.get('ref') not in expanders and x.get('ref') not in removed and not (x.get('ref') in ['J41','J42'] and x.get('pin') in ['1','2']))
  if pts:result.add(pts)
 return result
check(groups(r)==groups(before),'Every retained non-expander pin has exactly the same connectivity as before (excluding menu lamp pins)')
# Check pin numbers, functions and native footprint pad numbering/geometry.
s=parse(Path('IEEEArcade.kicad_sch').read_text());libs=s.child('lib_symbols').children('symbol')
expected={'Memory_EEPROM:24LC256':{'1':'A0','2':'A1','3':'A2','4':'GND','5':'SDA','6':'SCL','7':'WP','8':'VCC'},'Interface_Expansion:MCP23017x-x-SO':{**{str(i+1):f'GPB{i}' for i in range(8)},**{str(i+21):f'GPA{i}' for i in range(8)},'9':'V_{DD}','10':'V_{SS}','11':'NC','12':'SCK','13':'SDA','14':'NC','15':'A0','16':'A1','17':'A2','18':'~{RESET}','19':'INTB','20':'INTA'}}
for name,pins in expected.items():
 lib=next(l for l in libs if l.items[1]==name);p={p.val('number'):p for sub in lib.children('symbol') for p in sub.children('pin')}
 check({n:p.val('name') for n,p in p.items()}==pins,name+' complete symbol pin functions match datasheet SOIC pinout')
 if '23017' in name:check(all(p[n].items[1]=='output' for n in ['8','28']),'MCP23017 GPB7/GPA7 are output-type pins in symbol')
for ref,count,foot,pad1,padlast in [('U3',8,'Package_SO:SOIC-8_3.9x4.9mm_P1.27mm',(-2.475,-1.905),(2.475,-1.905)),('U1',28,'Package_SO:SOIC-28W_7.5x17.9mm_P1.27mm',(-4.65,-8.255),(4.65,-8.255))]:
 check(components[ref].findtext('footprint')==foot,ref+' assigned correct SOIC package footprint')
 lib,n=foot.split(':');fp=parse((Path('C:/Program Files/KiCad/10.0/share/kicad/footprints')/(lib+'.pretty')/(n+'.kicad_mod')).read_text());pads={n.items[1]:n for n in fp.children('pad')}
 check(set(pads)=={str(n) for n in range(1,count+1)},foot+' pad numbering matches symbol')
 for no,xy in [('1',pad1),(str(count),padlast)]:check(tuple(float(v) for v in pads[no].child('at').items[1:3])==xy,foot+' pad'+no+' location matches SOIC orientation/pitch')
for ref in expanders:check(components[ref].findtext('footprint')==components['U1'].findtext('footprint'),ref+' uses verified wide SOIC-28 footprint')
# No new ERC findings; compare type, severity and item UUIDs.
def erc(file):
 d=json.loads(Path(file).read_text());return [(v['type'],v['severity'],(v['description'],) if v['type']=='four_way_junction' else tuple(sorted(x['uuid'] for x in v['items']))) for sh in d['sheets'] for v in sh['violations']]
b=erc('Review/ERC-before-io.json');a=erc('Review/ERC-io.json')
check(not(set(a)-set(b)),'ERC contains no new findings relative to pre-edit baseline')
checks.append('ERC baseline: '+str(collections.Counter((x[0],x[1]) for x in b)))
checks.append('ERC revised: '+str(collections.Counter((x[0],x[1]) for x in a)))
Path('Review/io-connectivity-verification.txt').write_text('\n'.join(checks)+'\n')
print('\n'.join(checks[-18:]));print('Total assertions:',len(checks)-2)
